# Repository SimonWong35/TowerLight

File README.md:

# TowerLight

This PCB is to Transmit the status of four 24v-input to its recipient through LoRa module.

## Schematic

## Layout (64mm x 93mm)

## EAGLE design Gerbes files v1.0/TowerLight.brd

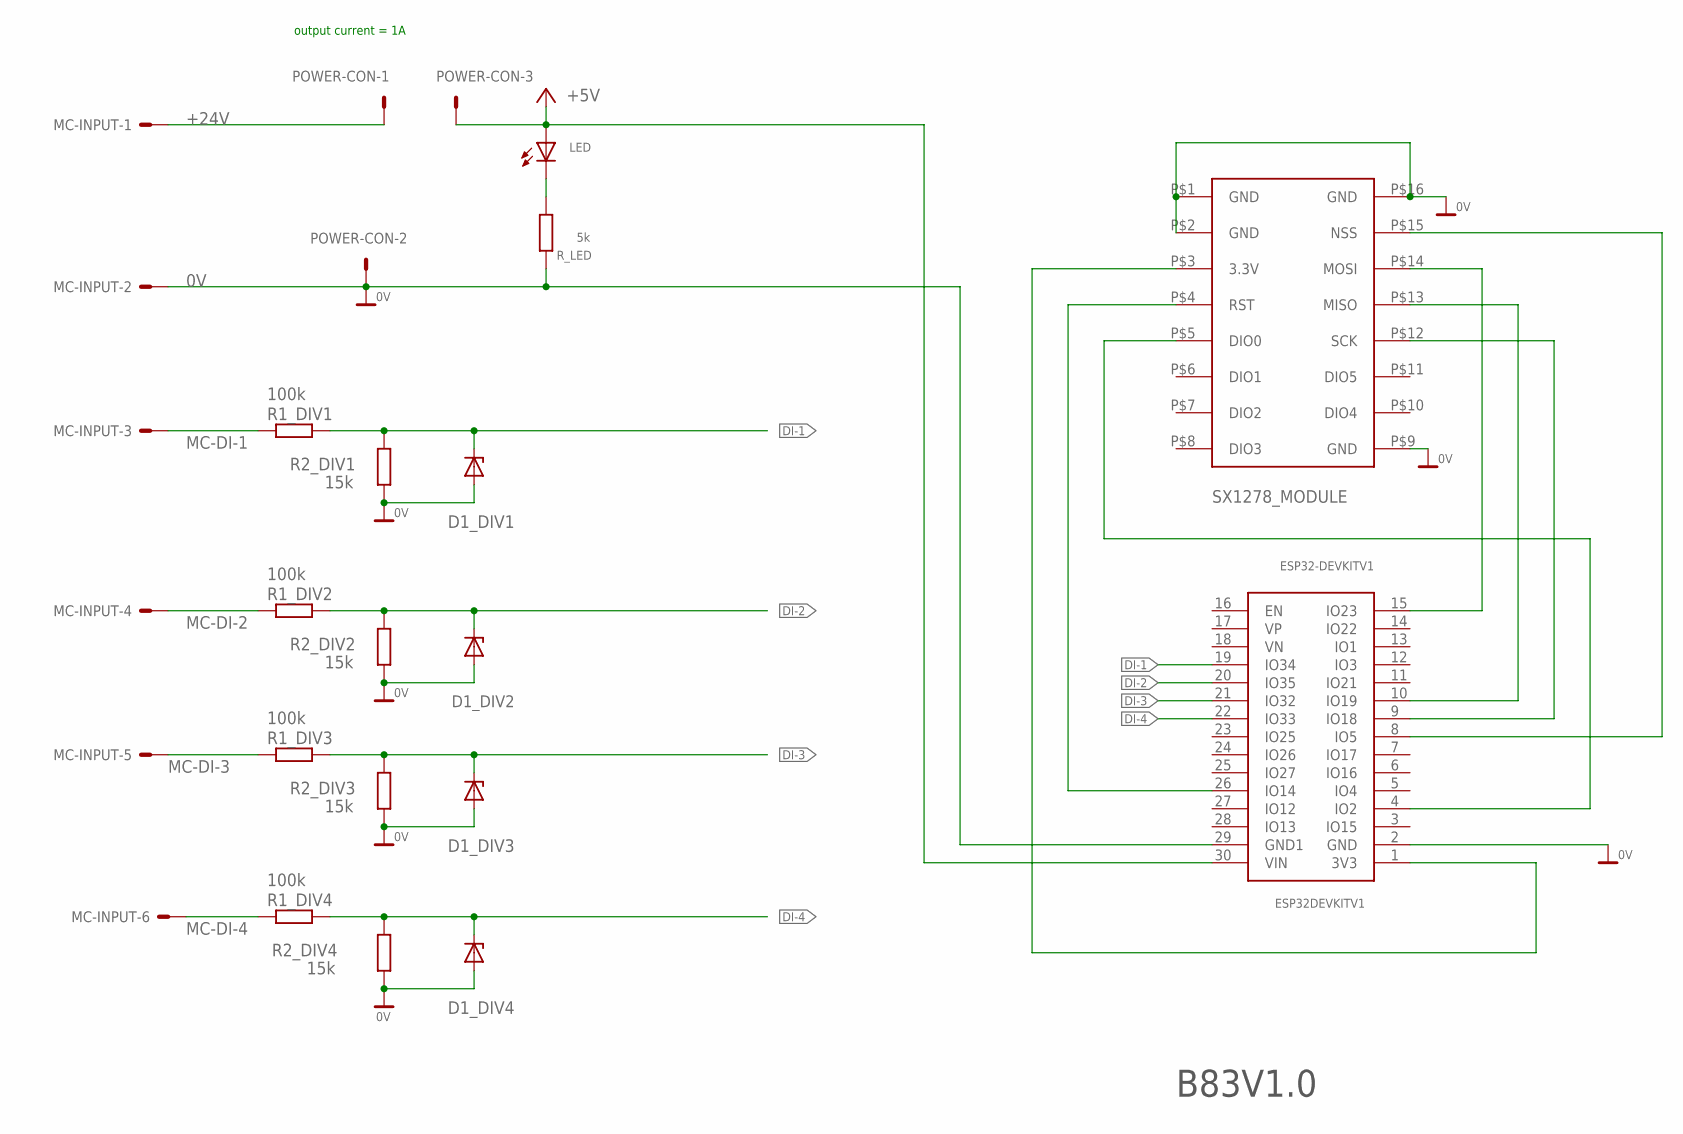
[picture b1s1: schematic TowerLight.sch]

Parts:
D1_DIV1, D1_DIV2, D1_DIV3, D1_DIV4: ZENER-DIODEDO34-7; DO34Z7
ESP32DEVKITV1: ESP32DEVKITV1; ESP32-DEVKITV1
LED: LED_SUB; LED_SUBMINI
MC-INPUT: 22-05-7068-06; 7395-06
POWER-CON: 22-05-7038-03; 7395-03
R1_DIV1, R1_DIV2, R1_DIV3, R1_DIV4: 100k; R1206
R2_DIV1, R2_DIV2, R2_DIV3, R2_DIV4: 15k; R1206
R_LED: 5k; R1206
U$2: LORA-02_SX1278_MODULE

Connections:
0V: D1_DIV1.A, D1_DIV2.A, D1_DIV3.A, D1_DIV4.A, ESP32DEVKITV1.2 (GND), ESP32DEVKITV1.29 (GND1), MC-INPUT.2, POWER-CON.2, R2_DIV1.1, R2_DIV2.1, R2_DIV3.1, R2_DIV4.1, R_LED.2, U$2.P$1 (GND), U$2.P$2 (GND), U$2.P$9 (GND), U$2.P$16 (GND)
+3V3: ESP32DEVKITV1.30 (VIN), LED.P$1 (A), POWER-CON.3
+24V: MC-INPUT.1, POWER-CON.1
DI-1: D1_DIV1.C, ESP32DEVKITV1.19 (IO34), R1_DIV1.2, R2_DIV1.2
DI-2: D1_DIV2.C, ESP32DEVKITV1.20 (IO35), R1_DIV2.2, R2_DIV2.2
DI-3: D1_DIV3.C, ESP32DEVKITV1.21 (IO32), R1_DIV3.2, R2_DIV3.2
DI-4: D1_DIV4.C, ESP32DEVKITV1.22 (IO33), R1_DIV4.2, R2_DIV4.2
MC-DI-1: MC-INPUT.3, R1_DIV1.1
MC-DI-2: MC-INPUT.4, R1_DIV2.1
MC-DI-3: MC-INPUT.5, R1_DIV3.1
MC-DI-4: MC-INPUT.6, R1_DIV4.1
unnamed: ESP32DEVKITV1.9 (IO18), U$2.P$12 (SCK)
unnamed: LED.P$2 (C), R_LED.1
unnamed: ESP32DEVKITV1.10 (IO19), U$2.P$13 (MISO)
unnamed: ESP32DEVKITV1.15 (IO23), U$2.P$14 (MOSI)
unnamed: ESP32DEVKITV1.8 (IO5), U$2.P$15 (NSS)
unnamed: ESP32DEVKITV1.4 (IO2), U$2.P$5 (DIO0)
unnamed: ESP32DEVKITV1.1 (3V3), U$2.P$3 (3.3V)
unnamed: ESP32DEVKITV1.26 (IO14), U$2.P$4 (RST)

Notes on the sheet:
B83V1.0
output current = 1A

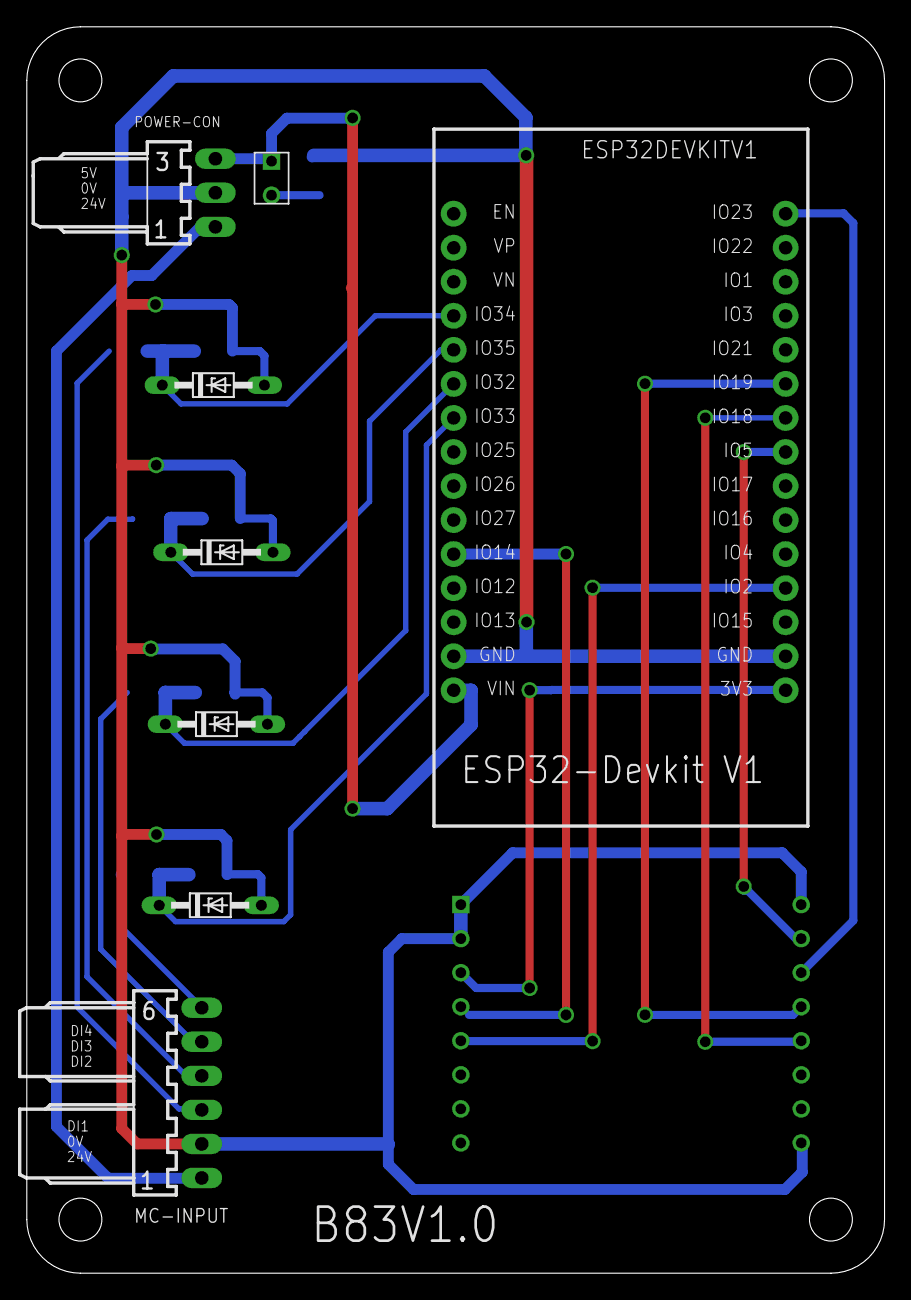
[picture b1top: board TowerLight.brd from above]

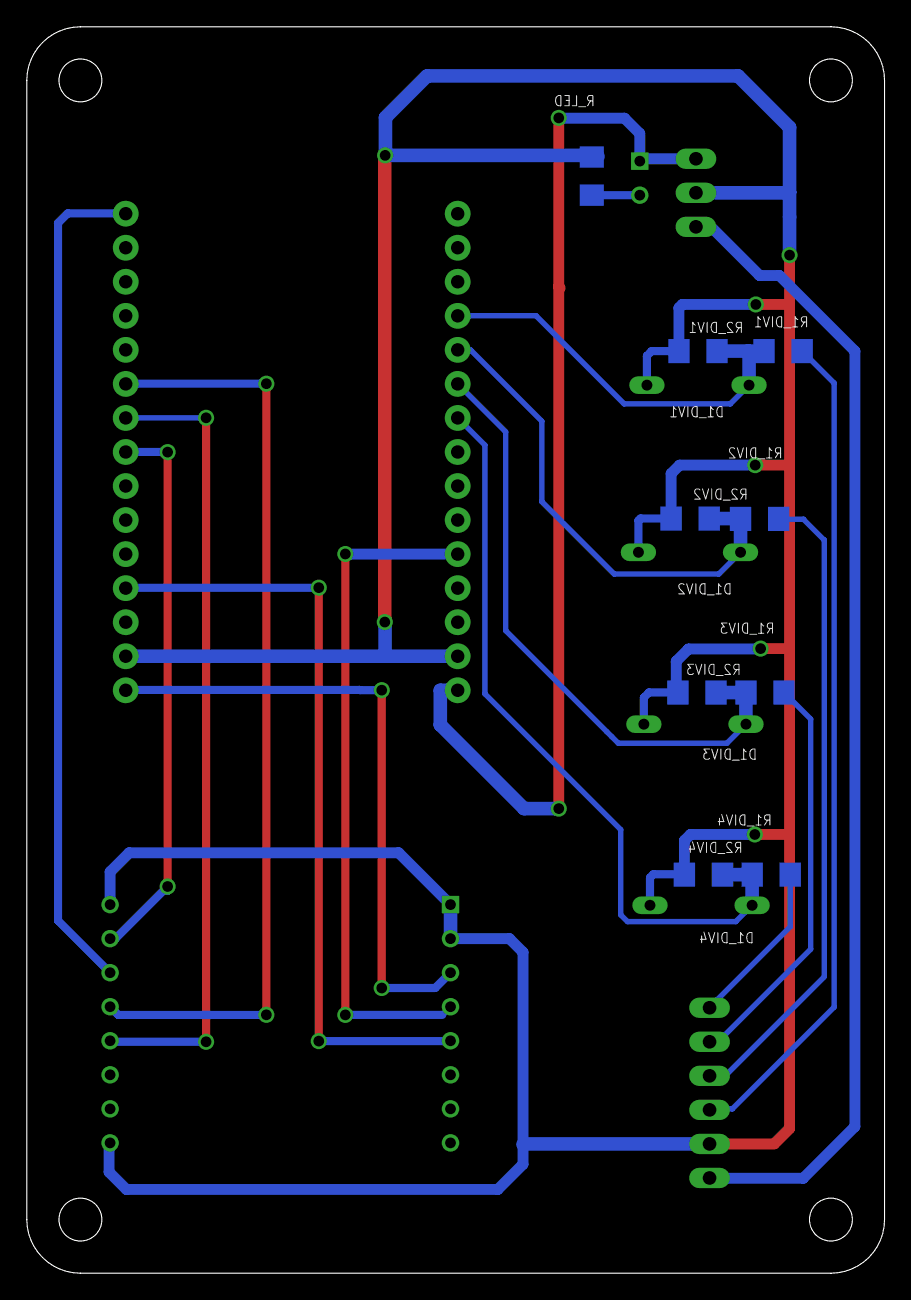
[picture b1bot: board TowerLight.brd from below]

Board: 2 copper layers, 64.0 x 93.0 mm, 18 parts (9 on the bottom side), 19 nets.
